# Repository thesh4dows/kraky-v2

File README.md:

# kraky-v2
Kraky2 is the second version of the DIY and open-hardware poject inspired by the Flipper Zero.
It uses the esp32-S3 microntroller to manage all the different modules like the NFC,RFID, and some.

The module is divided in 2 layers, the front one houses the esp32, Wifi and Sub-GHz antennas, buttons, IR and a part of the
power delivery system; the back one houses the NFC and RFID modules on top of the rest of the power delivery system.

Using the four buttons you can take advantage of all the modules that composes the kraky2, you can also use it connected to 
a battery or via the usb-c port that is integrated in the circuit.

I would suggest putting first the esp32 as is the most difficult part to put, then the others chip, all the capacitors, resistors, inductors and so on and for last all the
tht components because they are the ones that pass through the board so they are more simple to put.

I started this journey because i want to create a better version of my project kraky, and i'm doing it by first using smd components instead of the 
tht modules so i can do some expirience soldering very small parts and stopping using pre made modules but recreating them myself.
420.65
---

# Main Components
| Function | Component |
|--------|----------|
| Logic board | **ESP32-S3 N16R8** |
| wifi | **nrf24l01** |
| Sub-GHz | **CC1101** |
| RFID | **MFRC522** |
| NFC | **PN532** |
| Battery charger | **CN3163** |
| Battery | Li-ion |
| IR Receiver | **TSOP38238** |
| IR Transmitter | IR LED |
| microSD Slot | **MSD4A** |
| Buttons | 4 tactile buttons |
| Display | TFT Display |

---

# WIRING DIAGRAM

# ESP32

 # POWER DELIVERY SYSTEM

# IR

# WIFI

# SUB-GHZ

# MICROSD SLOT

# NFC

# RFID

# BUTTONS

# DISPLAY

---

# PCB

---

# 3D RENDER

---
# Responsible Use
Kraky2 is built to make it easier for anyone to explore and understand how multifunction electronic devices work in everyday life. It’s not intended for bypassing security systems or breaking any laws.

All features are implemented with an educational and experimental focus.

---

# Zine page

---

# Tools Used

- KiCad 10
- Fusion360
- PlatformIO
---
## Contributing

Kraky is an **open and educational project**.  
Feedback, suggestions, and improvements are always welcome.

---

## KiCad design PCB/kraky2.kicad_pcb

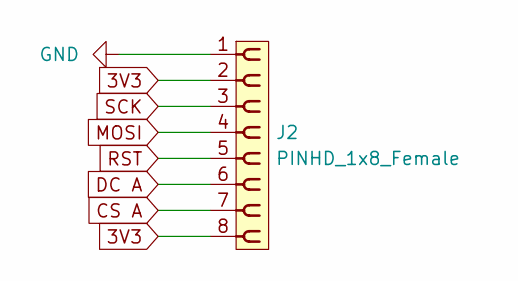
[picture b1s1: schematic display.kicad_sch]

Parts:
J2: PINHD_1x8_Female; PinSocket_1x08_P2.54mm_Vertical

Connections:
3V3: J2.2, J2.8; also elsewhere on the board
CS A: J2.7; also elsewhere on the board
DC A: J2.6; also elsewhere on the board
GND: J2.1; also elsewhere on the board
MOSI: J2.4; also elsewhere on the board
RST A: J2.5; also elsewhere on the board
SCK: J2.3; also elsewhere on the board

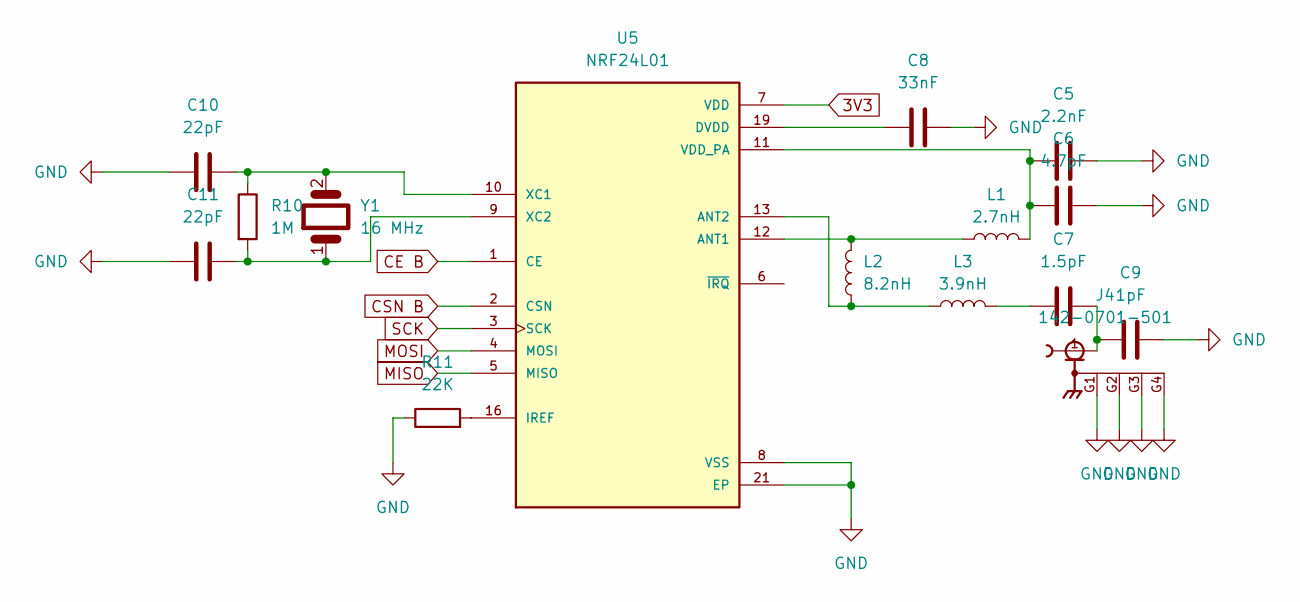
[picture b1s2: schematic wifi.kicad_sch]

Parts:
C5: 2.2nF; C_0805_2012Metric
C6: 4.7pF; C_0805_2012Metric
C7: 1.5pF; C_0805_2012Metric
C8: 33nF; C_0805_2012Metric
C9: 1pF; C_0805_2012Metric
C10, C11: 22pF; C_0805_2012Metric
J4: 142-0701-501; SMA_Molex_73251-1153_EdgeMount_Horizontal; PARTREV 7c
L1: 2.7nH; L_0805_2012Metric
L2: 8.2nH; L_0805_2012Metric
L3: 3.9nH; L_0805_2012Metric
R10: 1M; R_0805_2012Metric
R11: 22K; R_0805_2012Metric
U5: NRF24L01; QFN50P400X400X95-21N; PARTREV 2.0
Y1: 16 MHz; Crystal_SMD_5032-2Pin_5.0x3.2mm_HandSoldering

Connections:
3V3: U5.7 (VDD), U5.15 (VDD), U5.18 (VDD); also elsewhere on the board
CE B: U5.1 (CE); also elsewhere on the board
CSN B: U5.2 (CSN); also elsewhere on the board
GND: C5.2, C6.2, C8.2, C9.2, C10.1, C11.1, J4.G1, J4.G2, J4.G3, J4.G4, R11.1, U5.8 (VSS), U5.14 (VSS), U5.17 (VSS), U5.20 (VSS), U5.21 (EP); also elsewhere on the board
MISO: U5.5 (MISO); also elsewhere on the board
MOSI: U5.4 (MOSI); also elsewhere on the board
unnamed: C7.1, L3.2
unnamed: C7.2, C9.1, J4.1
unnamed: L1.1, L2.2, U5.12 (ANT1)
unnamed: L2.1, L3.1, U5.13 (ANT2)
unnamed: C8.1, U5.19 (DVDD)
unnamed: R11.2, U5.16 (IREF)
unnamed: C5.1, C6.1, L1.2, U5.11 (VDD_PA)
unnamed: C10.2, R10.1, U5.10 (XC1), Y1.2
unnamed: C11.2, R10.2, U5.9 (XC2), Y1.1
SCK: U5.3 (SCK); also elsewhere on the board

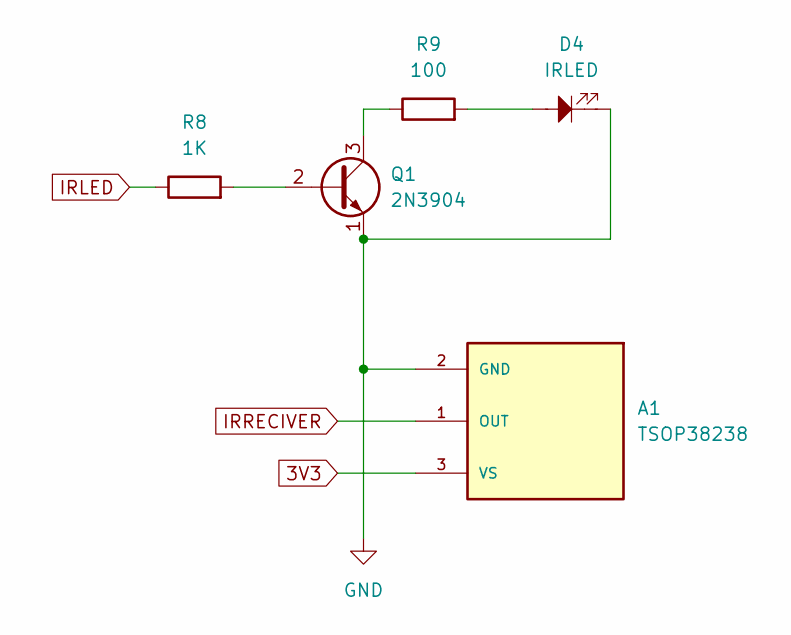
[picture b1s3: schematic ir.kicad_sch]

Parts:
A1: TSOP38238; XDCR_TSOP38238; PARTREV 1.7
D4: IRLED; WL-SISW_1002_15410294AA570
Q1: 2N3904; SOT-23_Handsoldering
R8: 1K; R_0805_2012Metric
R9: 100; R_0805_2012Metric

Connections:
3V3: A1.3 (VS); also elsewhere on the board
GND: A1.2 (GND), D4.1, Q1.1 (E); also elsewhere on the board
IRLED: R8.1; also elsewhere on the board
IRRECIVER: A1.1 (OUT); also elsewhere on the board
unnamed: D4.2, R9.2
unnamed: Q1.2 (B), R8.2
unnamed: Q1.3 (C), R9.1

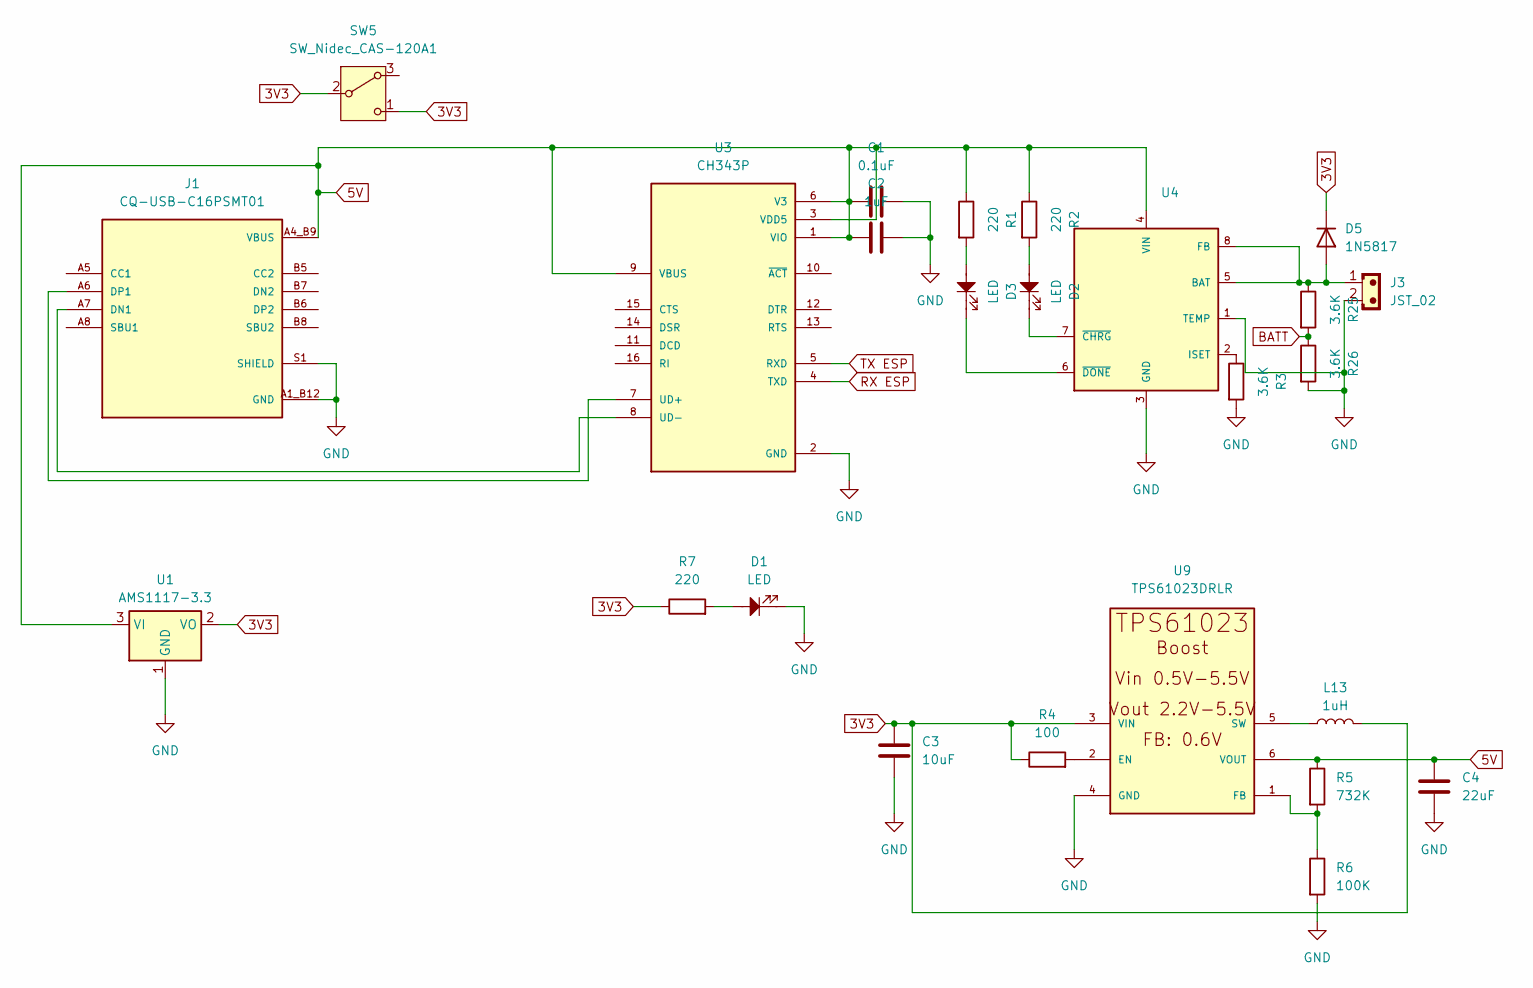
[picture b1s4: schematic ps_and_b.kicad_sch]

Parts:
C1: 0.1uF; C_0805_2012Metric
C2: 1uF; C_0805_2012Metric
C3: 10uF; C_0805_2012Metric
C4: 22uF; C_0805_2012Metric
D1, D2, D3: LED; LED_1206_3216Metric
D5: 1N5817; D_SMA_Handsoldering
J1: CQ-USB-C16PSMT01; SHENZHEN-CHUANGQIN-TECHNOLOGY_CQ-USB-C16PSMT01; PARTREV A
J3: JST_02; JST_EH_B2B-EH-A_1x02_P2.50mm_Vertical
L13: 1uH; L_0805_2012Metric
R1, R2, R7: 220; R_0805_2012Metric
R3, R25, R26: 3.6K; R_0805_2012Metric
R4: 100; R_0805_2012Metric
R5: 732K; R_0805_2012Metric
R6: 100K; R_0805_2012Metric
SW5: SW_Nidec_CAS-120A1; SW_Slide_SPDT_Angled_CK_OS102011MA1Q
U1: AMS1117-3.3; SOT-223-3_TabPin2
U3: CH343P; QFN50P300X300X80-17N; PARTREV 1E
U4: CN3063-SOIC8; SOIC8-1.27-5X4MM; MPN CN3063
U9: TPS61023DRLR; SOT563-ORI

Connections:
3V3: C3.1, D5.1 (K), L13.2, R4.1, R7.1, SW5.1 (C), SW5.2 (B), U1.2 (VO), U9.3 (VIN); also elsewhere on the board
5V: C1.1, C2.1, C4.1, J1.A4_B9 (VBUS), J1.B4_A9 (VBUS), R1.1, R2.1, R5.1, U1.3 (VI), U3.1 (VIO), U3.3 (VDD5), U3.6 (V3), U3.9 (VBUS), U4.4 (VIN), U9.6 (VOUT); also elsewhere on the board
BATT: R25.2, R26.1; also elsewhere on the board
GND: C1.2, C2.2, C3.2, C4.2, D1.1, J1.A1_B12 (GND), J1.B1_A12 (GND), J1.S1 (SHIELD), J1.S2 (SHIELD), J1.S3 (SHIELD), J1.S4 (SHIELD), J3.2, R3.2, R6.2, R26.2, U1.1 (GND), U3.2 (GND), U3.17 (GND), U4.1 (TEMP), U4.3 (GND), U9.4 (GND); also elsewhere on the board
unnamed: D1.2, R7.2
unnamed: D2.2, R2.2
unnamed: D3.2, R1.2
unnamed: D5.2 (A), J3.1, R25.1, U4.5 (BAT), U4.8 (FB)
unnamed: J1.A7 (DN1), U3.8 (UD-)
unnamed: J1.A6 (DP1), U3.7 (UD+)
unnamed: R3.1, U4.2 (ISET)
unnamed: D2.1, U4.7 (~CHRG)
unnamed: D3.1, U4.6 (~DONE)
unnamed: R4.2, U9.2 (EN)
unnamed: R5.2, R6.1, U9.1 (FB)
unnamed: L13.1, U9.5 (SW)
RX ESP: U3.4 (TXD); also elsewhere on the board
TX ESP: U3.5 (RXD); also elsewhere on the board

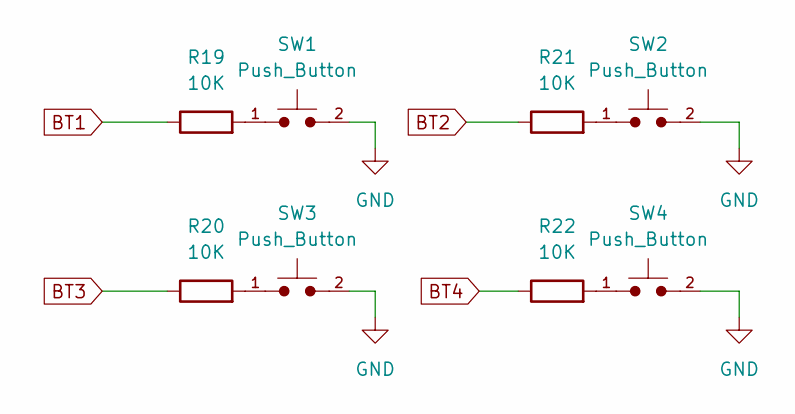
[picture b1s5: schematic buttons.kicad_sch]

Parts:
R19, R20, R21, R22: 10K; R_0805_2012Metric
SW1, SW2, SW3, SW4: Push_Button; SW_SPST_PTS645Sx43SMTR92

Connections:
BT1: R19.1; also elsewhere on the board
BT2: R21.1; also elsewhere on the board
BT3: R20.1; also elsewhere on the board
BT4: R22.1; also elsewhere on the board
GND: SW1.2, SW2.2, SW3.2, SW4.2; also elsewhere on the board
unnamed: R19.2, SW1.1
unnamed: R20.2, SW3.1
unnamed: R21.2, SW2.1
unnamed: R22.2, SW4.1

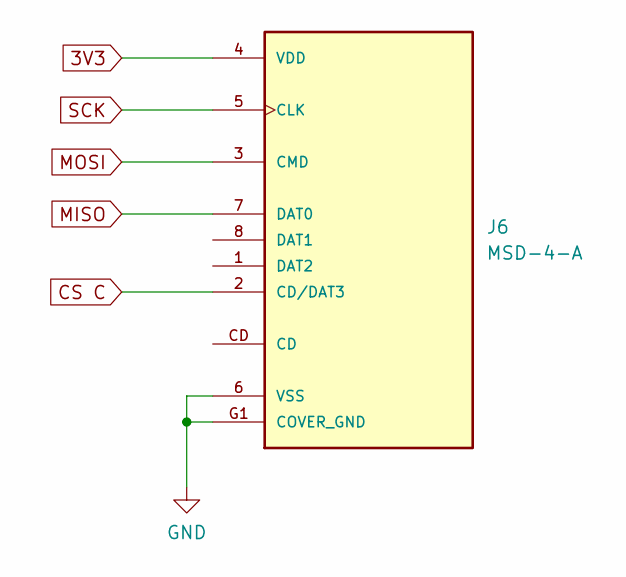
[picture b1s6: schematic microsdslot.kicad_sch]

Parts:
J6: MSD-4-A; CUI_MSD-4-A; PARTREV 1.0

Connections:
3V3: J6.4 (VDD); also elsewhere on the board
CS C: J6.2 (CD/DAT3); also elsewhere on the board
GND: J6.6 (VSS), J6.G1 (COVER_GND), J6.G2 (COVER_GND), J6.G3 (COVER_GND), J6.G4 (COVER_GND); also elsewhere on the board
MISO: J6.7 (DAT0); also elsewhere on the board
MOSI: J6.3 (CMD); also elsewhere on the board
SCK: J6.5 (CLK); also elsewhere on the board

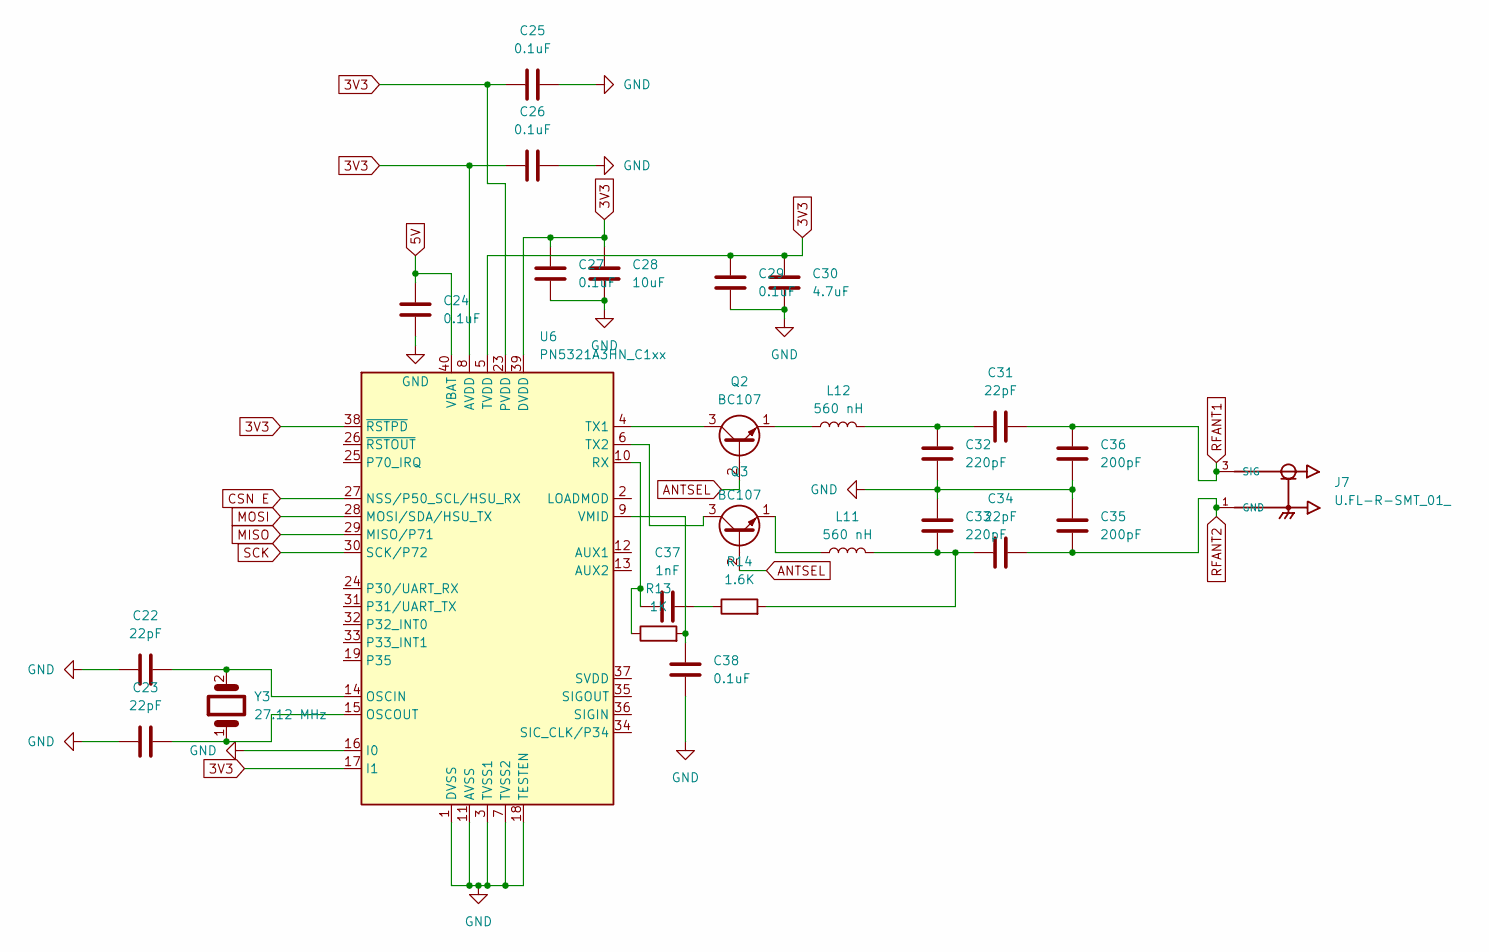
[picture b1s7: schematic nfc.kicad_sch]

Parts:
C22, C23, C31, C34: 22pF; C_0805_2012Metric
C24, C25, C26, C27, C29, C38: 0.1uF; C_0805_2012Metric
C28: 10uF; C_0805_2012Metric
C30: 4.7uF; C_0805_2012Metric
C32, C33: 220pF; C_0805_2012Metric
C35, C36: 200pF; C_0805_2012Metric
C37: 1nF; C_0805_2012Metric
J7: U.FL-R-SMT_01_; HRS_U.FL-R-SMT_01_
L11, L12: 560 nH; L_0805_2012Metric
Q2, Q3: BC107; SOT-23_Handsoldering
R13: 1K; R_0805_2012Metric
R14: 1.6K; R_0805_2012Metric
U6: PN5321A3HN_C1xx; HVQFN-40-1EP_6x6mm_P0.5mm_EP4.1x4.1mm_ThermalVias
Y3: 27.12 MHz; Crystal_SMD_5032-2Pin_5.0x3.2mm_HandSoldering

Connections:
3V3: C25.1, C26.1, C27.1, C28.1, C29.1, C30.1, U6.5 (TVDD), U6.8 (AVDD), U6.17 (I1), U6.23 (PVDD), U6.38 (~RSTPD), U6.39 (DVDD); also elsewhere on the board
5V: C24.1, U6.40 (VBAT); also elsewhere on the board
ANTSEL: Q2.2 (B), Q3.2 (B); also elsewhere on the board
CSN E: U6.27 (NSS/P50_SCL/HSU_RX); also elsewhere on the board
GND: C22.1, C23.1, C24.2, C25.2, C26.2, C27.2, C28.2, C29.2, C30.2, C32.1, C33.2, C35.1, C36.2, C38.2, U6.1 (DVSS), U6.3 (TVSS1), U6.7 (TVSS2), U6.11 (AVSS), U6.16 (I0), U6.18 (TESTEN), U6.41 (AVSS); also elsewhere on the board
MISO: U6.29 (MISO/P71); also elsewhere on the board
MOSI: U6.28 (MOSI/SDA/HSU_TX); also elsewhere on the board
unnamed: C31.1, C32.2, L12.2
unnamed: C33.1, C34.1, L11.2, R14.2
unnamed: C37.2, R14.1
unnamed: Q2.3 (C), U6.4 (TX1)
unnamed: L12.1, Q2.1 (E)
unnamed: Q3.3 (C), U6.6 (TX2)
unnamed: L11.1, Q3.1 (E)
unnamed: C22.2, U6.14 (OSCIN), Y3.2
unnamed: C23.2, U6.15 (OSCOUT), Y3.1
unnamed: C37.1, R13.1, U6.10 (RX)
unnamed: C38.1, R13.2, U6.9 (VMID)
RFANT1: C31.2, C36.1, J7.3 (SIG); also elsewhere on the board
RFANT2: C34.2, C35.2, J7.1 (GND), J7.2 (GND); also elsewhere on the board
SCK: U6.30 (SCK/P72); also elsewhere on the board

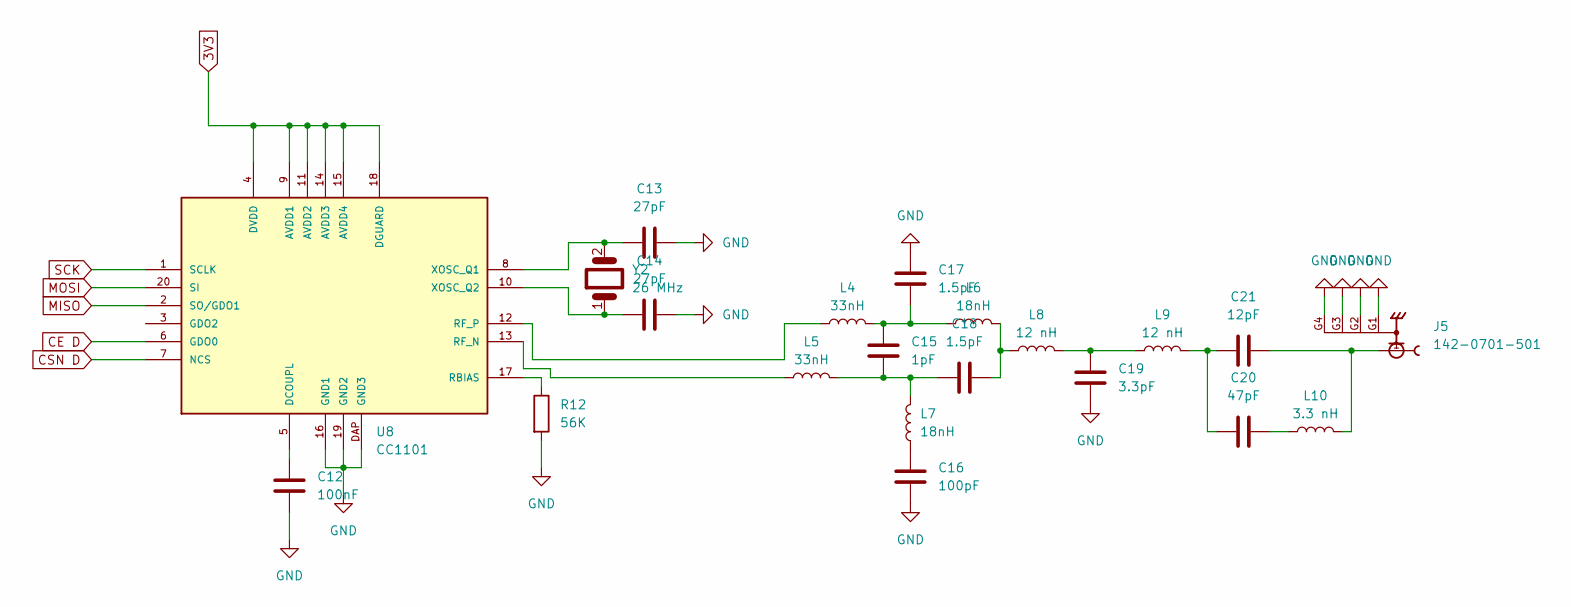
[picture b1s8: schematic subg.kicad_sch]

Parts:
C12: 100nF; C_0805_2012Metric
C13, C14: 27pF; C_0805_2012Metric
C15: 1pF; C_0805_2012Metric
C16: 100pF; C_0805_2012Metric
C17, C18: 1.5pF; C_0805_2012Metric
C19: 3.3pF; C_0805_2012Metric
C20: 47pF; C_0805_2012Metric
C21: 12pF; C_0805_2012Metric
J5: 142-0701-501; SMA_Molex_73251-1153_EdgeMount_Horizontal; PARTREV 7c
L4, L5: 33nH; L_0805_2012Metric
L6, L7: 18nH; L_0805_2012Metric
L8, L9: 12 nH; L_0805_2012Metric
L10: 3.3 nH; L_0805_2012Metric
R12: 56K; R_0805_2012Metric
U8: CC1101; QLP20
Y2: 26 MHz; Crystal_SMD_5032-2Pin_5.0x3.2mm_HandSoldering

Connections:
3V3: U8.4 (DVDD), U8.9 (AVDD1), U8.11 (AVDD2), U8.14 (AVDD3), U8.15 (AVDD4), U8.18 (DGUARD); also elsewhere on the board
CE D: U8.6 (GDO0); also elsewhere on the board
CSN D: U8.7 (NCS); also elsewhere on the board
GND: C12.1, C13.2, C14.2, C16.1, C17.2, C19.1, J5.G1, J5.G2, J5.G3, J5.G4, R12.2, U8.16 (GND1), U8.19 (GND2), U8.DAP (GND3); also elsewhere on the board
MISO: U8.2 (SO/GDO1); also elsewhere on the board
MOSI: U8.20 (SI); also elsewhere on the board
unnamed: C15.1, C18.2, L5.2, L7.2
unnamed: C15.2, C17.1, L4.2, L6.1
unnamed: C16.2, L7.1
unnamed: C18.1, L6.2, L8.1
unnamed: C19.2, L8.2, L9.1
unnamed: C20.1, C21.1, L9.2
unnamed: C20.2, L10.1
unnamed: C21.2, J5.1, L10.2
unnamed: C12.2, U8.5 (DCOUPL)
unnamed: R12.1, U8.17 (RBIAS)
unnamed: L5.1, U8.13 (RF_N)
unnamed: L4.1, U8.12 (RF_P)
unnamed: C13.1, U8.8 (XOSC_Q1), Y2.2
unnamed: C14.1, U8.10 (XOSC_Q2), Y2.1
SCK: U8.1 (SCLK); also elsewhere on the board

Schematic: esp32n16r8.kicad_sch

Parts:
R23, R24: 10K; R_0805_2012Metric
SW6: RESET; SW_SPST_EVQPE1
SW7: BOOT; SW_SPST_EVQPE1
U11: ESP32-S3-WROOM-1

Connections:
3V3: U11.2 (3V3); also elsewhere on the board
ANTSEL: U11.5 (IO5); also elsewhere on the board
ANTSEL1: U11.7 (IO7); also elsewhere on the board
BATT: U11.17 (IO9); also elsewhere on the board
BT1: U11.31 (IO38); also elsewhere on the board
BT2: U11.32 (IO39); also elsewhere on the board
BT3: U11.33 (IO40); also elsewhere on the board
BT4: U11.34 (IO41); also elsewhere on the board
CE B: U11.4 (IO4); also elsewhere on the board
CE D: U11.38 (IO2); also elsewhere on the board
CS A: U11.16 (IO46); also elsewhere on the board
CS C: U11.12 (IO8); also elsewhere on the board
CSN B: U11.25 (IO48); also elsewhere on the board
CSN D: U11.15 (IO3); also elsewhere on the board
CSN E: U11.39 (IO1); also elsewhere on the board
CSN F: U11.6 (IO6); also elsewhere on the board
DC A: U11.24 (IO47); also elsewhere on the board
GND: SW6.1, SW7.1, U11.1 (GND), U11.40 (GND), U11.41 (GND); also elsewhere on the board
IRLED: U11.35 (IO42); also elsewhere on the board
IRRECIVER: U11.26 (IO45); also elsewhere on the board
MISO: U11.10 (IO17); also elsewhere on the board
MOSI: U11.11 (IO18); also elsewhere on the board
unnamed: R23.1, SW7.2
unnamed: R24.1, SW6.2
unnamed: R23.2, U11.27 (IO0)
RST: R24.2, U11.3 (EN)
RST A: U11.18 (IO10); also elsewhere on the board
RX ESP: U11.36 (RXD0); also elsewhere on the board
SCK: U11.23 (IO21); also elsewhere on the board
TX ESP: U11.37 (TXD0); also elsewhere on the board

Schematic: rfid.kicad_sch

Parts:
C39, C40, C41, C42, C43, C44, C45, C46, C47, C48: 1uF; C_0805_2012Metric
L14, L15: 1 mH; L_0805_2012Metric
Q4, Q5: BC107; SOT-23_Handsoldering
R15, R16, R17, R18: 1K; R_0805_2012Metric
U10: MFRC522; QFN50P500X500X100-33N; PARTREV 3.9
Y4: 27.12 MHz; Crystal_SMD_5032-2Pin_5.0x3.2mm_HandSoldering

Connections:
3V3: U10.2 (PVDD), U10.3 (DVDD), U10.6 (~NRSTPD), U10.9 (SVDD), U10.12 (TVDD), U10.15 (AVDD); also elsewhere on the board
ANTSEL1: Q4.2 (B), Q5.2 (B); also elsewhere on the board
CSN F: U10.24 (SDA/NSS/RX); also elsewhere on the board
GND: C40.2, C41.2, C48.2, U10.4 (DVSS), U10.5 (PVSS), U10.10 (TVSS), U10.14 (TVSS), U10.18 (AVSS); also elsewhere on the board
MISO: U10.31 (D7/SCL/MISO/TX); also elsewhere on the board
MOSI: U10.30 (D6/ADR_0/MOSI/MX); also elsewhere on the board
unnamed: C39.2, R17.1
unnamed: C42.1, C45.1, L15.2
unnamed: C42.2, C47.1, R15.1
unnamed: C43.1, C44.2, L14.2
unnamed: C43.2, C46.2, R18.1
unnamed: C44.1, C45.2
unnamed: C46.1, C47.2
unnamed: Q4.3 (C), R17.2, U10.11 (TX1)
unnamed: L14.1, Q4.1 (E)
unnamed: Q5.3 (C), U10.13 (TX2)
unnamed: L15.1, Q5.1 (E)
unnamed: C41.1, U10.21 (OSCIN), Y4.2
unnamed: C48.1, U10.22 (OSCOUT), Y4.1
unnamed: C39.1, R16.1, U10.17 (RX)
unnamed: C40.1, R16.2, U10.16 (VMID)
RFANT1: R15.2; also elsewhere on the board
RFANT2: R18.2; also elsewhere on the board
SCK: U10.29 (D5/ADR_1/SCK/DTRQ); also elsewhere on the board

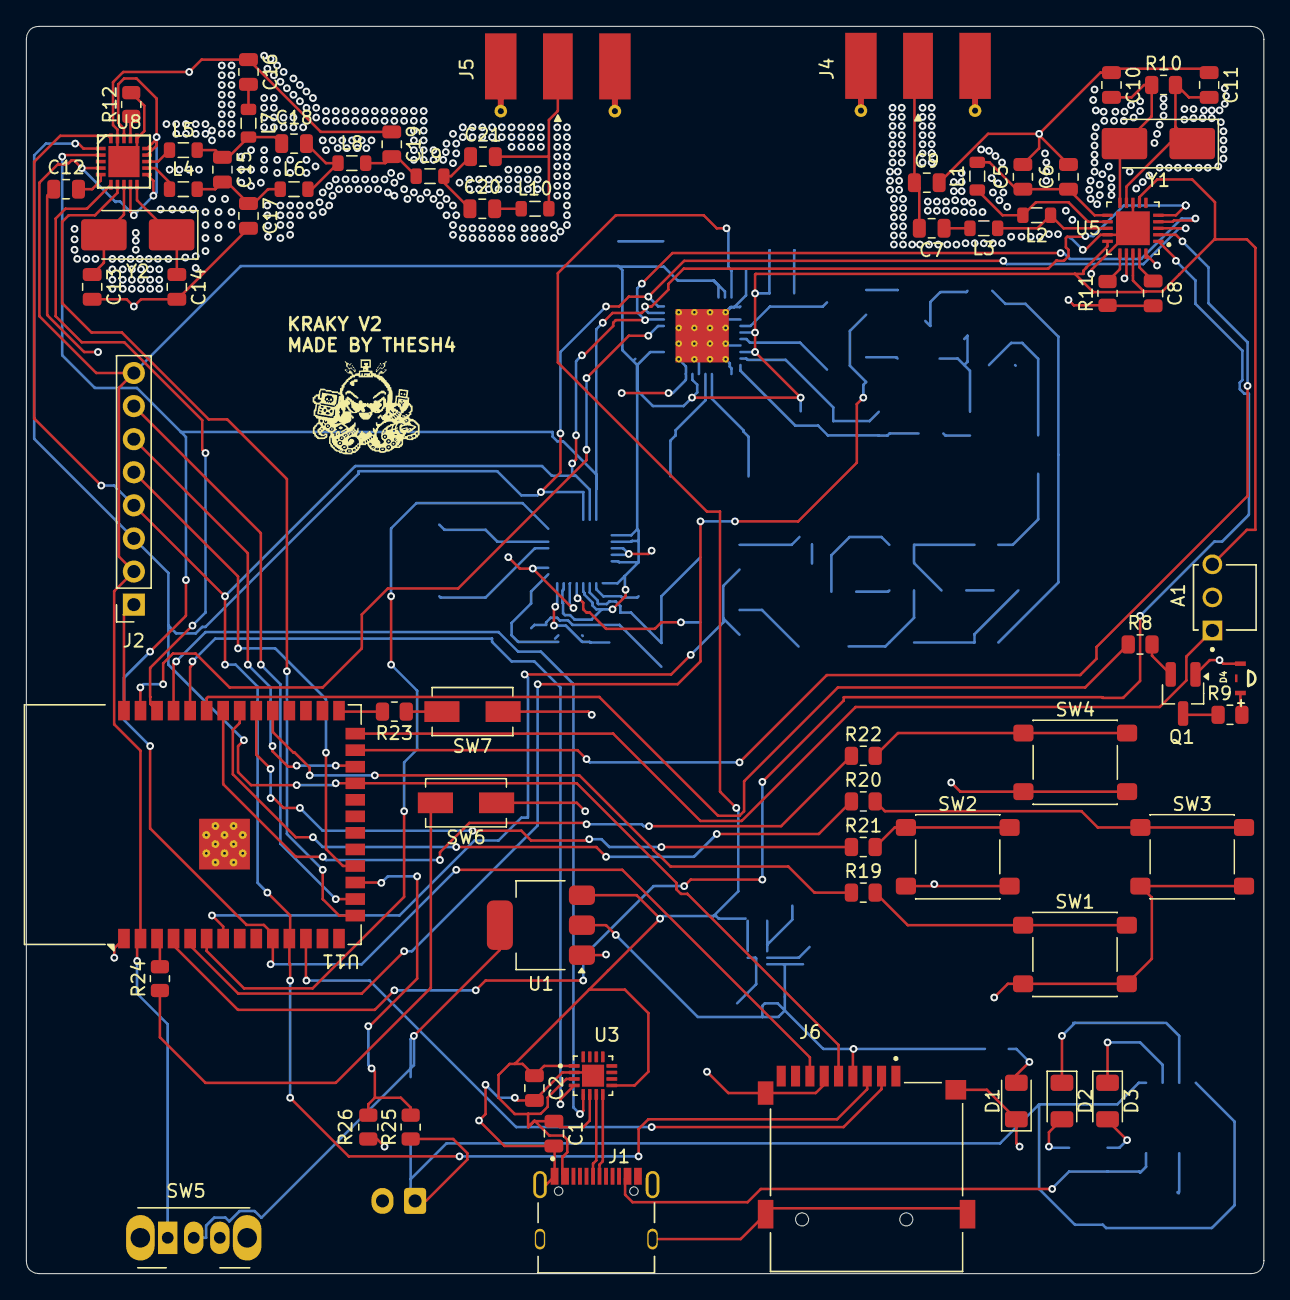
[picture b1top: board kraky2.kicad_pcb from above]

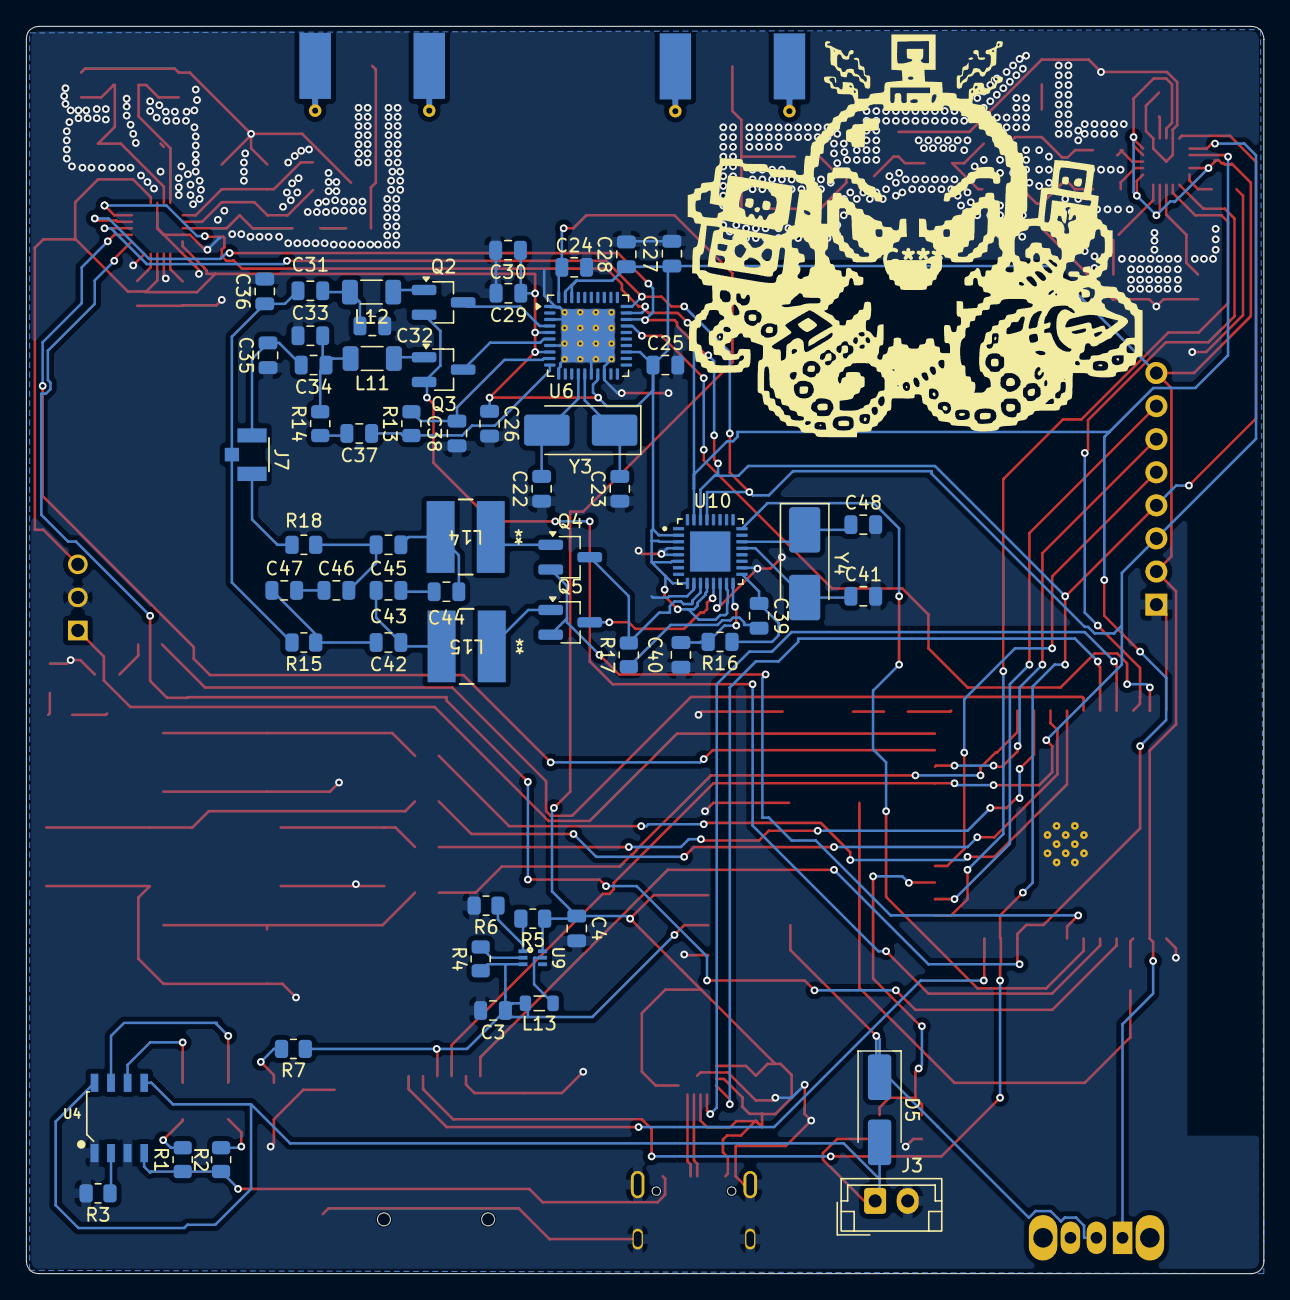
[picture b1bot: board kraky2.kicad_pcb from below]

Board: 2 copper layers, 95.0 x 95.8 mm, 127 parts (60 on the bottom side), 101 nets.

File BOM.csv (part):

name,value ,link,description,cost,quantity,added
resistor,,,,,,
R1,220,https://it.aliexpress.com/item/1005010070793079.html?spm=a2g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,805,1.45,3,
R2,220,R1,805,R1,R1,
R3,3.6K,https://it.aliexpress.com/item/1005010070793079.html?spm=a2g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,805,1.45,1,
R4,100,https://it.aliexpress.com/item/1005010070793079.html?spm=a2g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,805,1.45,2,
R5,732K,https://it.aliexpress.com/item/1005005184230104.html?spm=a2g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,805,2.07,1,
R6,100K,https://it.aliexpress.com/item/1005010070793079.html?spm=a2g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,805,1.45,3,
R7,220,R1,805,R1,R1,
R8,1K,https://it.aliexpress.com/item/1005010070793079.html?spm=a2g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,805,1.45,6,
R9,100,R4,805,R4,R4,
R10,1M,https://it.aliexpress.com/item/1005010070793079.html?spm=a2g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,805,1.46,1,
R11,22K,https://it.aliexpress.com/item/1005010070793079.html?spm=a2g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,805,1.45,1,
R12,56K,https://it.aliexpress.com/item/1005010070793079.html?spm=a2g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,805,1.45,1,
R13,1K,R8,805,R8,R8,
R14,1.6K,https://it.aliexpress.com/item/1005010070793079.html?spm=a2g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,805,1.45,1,
R15,1K,R8,805,R8,R8,
R16,1K,R8,805,R8,R8,
R17,1K,R8,805,R8,R8,
R18,1K,R8,805,R8,R8,
R19,10K,https://it.aliexpress.com/item/1005010070793079.html?spm=a2g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,805,1.45,6,
R20,10K,R19,805,R19,R19,
R21,10K,R19,805,R19,R19,
R22,10K,R19,805,R19,R19,
R23,10K,R19,805,R19,R19,
R24,10K,R19,805,R19,R19,
R25,100K,R6,805,R6,R6,
R26,100K,R6,805,R6,R6,
capacitor,,,,,,
C1,0.1 uF,https://it.aliexpress.com/item/1005005929029743.html?spm=a2g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,805,1.22,7,
C2,1 uF,https://it.aliexpress.com/item/1005005929029743.html?spm=a2g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,805,1.6,11,
C3,10 uF,https://it.aliexpress.com/item/1005005929029743.html?spm=a2g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,805,1.46,2,
C4,22 uF,https://it.aliexpress.com/item/1005005929029743.html?spm=a2g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,805,1.6,1,
C5,2.2 nF,https://it.aliexpress.com/item/1005005929029743.html?spm=a2g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,805,1.36,1,
C6,4.7 pF,https://it.aliexpress.com/item/1005005929029743.html?spm=a2g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,805,1.36,1,
C7,1.5 pF,https://it.aliexpress.com/item/1005005929029743.html?spm=a2g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,805,1.36,3,
C8,33 nF,https://it.aliexpress.com/item/1005005929029743.html?spm=a2g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,805,1.37,1,
C9,1 pF,https://it.aliexpress.com/item/1005005929029743.html?spm=a2g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,805,1.36,2,
C10,22 pF,https://it.aliexpress.com/item/1005005929029743.html?spm=a2g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,805,1.38,6,
C11,22 pF,C10,805,C10,C10,
C12,100 nF,https://it.aliexpress.com/item/1005005929029743.html?spm=a2g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,805,1.21,1,
C13,27 pF,https://it.aliexpress.com/item/1005005929029743.html?spm=a2g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,805,1.38,2,
C14,27 pF,C13,805,C13,C13,
C15,1 pF,C9,805,C9,C9,
C16,100 pF,https://it.aliexpress.com/item/1005005929029743.html?spm=a2g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,805,1.36,1,
C17,1.5 pF,C7,805,C7,C7,
C18,1.5pF,C7,805,C7,C7,
C19,3.3 pF,https://it.aliexpress.com/item/1005005929029743.html?spm=a2g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,805,1.38,1,
C20,47 pF,https://it.aliexpress.com/item/1005005929029743.html?spm=a2g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,805,1.38,1,
C21,12 pF,https://it.aliexpress.com/item/1005005929029743.html?spm=a2g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,805,1.38,1,
C22,22 pF,C10,805,C10,C10,
C23,22 pF,C10,805,C10,C10,
C24,0.1 uF,C1,805,C1,C1,
C25,0.1 uF,C1,805,C1,C1,
C26,0.1 uF,C1,805,C1,C1,
C27,0.1 uF,C1,805,C1,C1,
C28,10 uF,C3,805,C3,C3,
C29,0.1 uF,C1,805,C1,C1,
C30,4.7 uF,https://it.aliexpress.com/item/1005005929029743.html?spm=a2g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,805,1.6,1,
C31,22 pF,C10,805,C10,C10,
C32,220 pF,https://it.aliexpress.com/item/1005005929029743.html?spm=a2g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,805,1.38,2,
C33,220 pF,C32,805,C32,C32,
C34,22 pF,C10,805,C10,C10,
C35,200 pF,https://it.aliexpress.com/item/1005005929029743.html?spm=a2g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,805,1.38,2,
C36,200 pF,C35,805,C35,C35,
C37,1 nF,https://it.aliexpress.com/item/1005005929029743.html?spm=a2g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,805,1.37,1,
C38,0.1 uF,C1,805,C1,C1,
C39,1 uF,C2,805,C2,C2,
C40,1 uF,C2,805,C2,C2,
C41,1 uF,C2,805,C2,C2,
C42,1 uF,C2,805,C2,C2,
C43,1 uF,C2,805,C2,C2,
C44,1 uF,C2,805,C2,C2,
C45,1 uF,C2,805,C2,C2,
C46,1 uF,C2,805,C2,C2,
C47,1 uF,C2,805,C2,C2,
C48,1 uF,C2,805,C2,C2,
inductor,,,,,,
L1,2.7 nH,https://it.aliexpress.com/item/1005003062755166.html?spm=a2g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,805,1.65,1,
L2,8.2 nH,https://it.aliexpress.com/item/1005003062755166.html?spm=a2g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,805,1.62,1,
L3,3.9 nH,https://it.aliexpress.com/item/1005003062755166.html?spm=a2g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,805,1.62,1,
L4,33 nH,https://it.aliexpress.com/item/1005006165931240.html?spm=a2g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,805,5.47,2,
L5,33 nH,L4,805,L4,L4,
L6,18 nH,https://it.aliexpress.com/item/1005003062755166.html?spm=a2g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,805,1.62,2,
L7,18 nH,L6,805,L6,L6,
L8,12 nH,https://it.aliexpress.com/item/1005003062755166.html?spm=a2g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,805,1.65,2,
L9,12 nH,L8,805,L8,L8,
L10,3.3 nH,https://it.aliexpress.com/item/1005003062755166.html?spm=a2g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,805,1.62,1,
L11,560 nH,https://it.aliexpress.com/item/1005003091167117.html?spm=a2g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,1210,1.99,2,
L12,560 nH,L11,1210,L11,L11,
L13,1 uH,https://it.aliexpress.com/item/1005003827404196.html?spm=a2g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,805,3.89,1,
L14,1 mH,https://it.aliexpress.com/item/4001191068539.html?spm=a2g0o.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,805,1.6,2,
L15,1 mH,L14,805,L14,L14,
crystal,,,,,,
Y1,16 MHz,https://it.aliexpress.com/item/1005007210644647.html?spm=a2g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,5032,3.16,1,
Y2,26 MHz,https://it.aliexpress.com/item/1005004711354176.html?spm=a2g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,5032,2.79,1,
Y3,27.12 MHz,https://it.aliexpress.com/item/1005004711354176.html?spm=a2g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,5032,2.75,2,
Y4,27.12MHz,Y3,5032,Y3,Y3,
buttons,,,,,,
SW1,navigation,https://it.aliexpress.com/item/1005006870284823.html?spm=a2g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,smd  6x6 mm,1.69,4,
SW2,navigation,SW1,smd  6x6 mm,SW1,SW1,
SW3,navigation,SW1,smd  6x6 mm,SW1,SW1,
SW4,navigation,SW1,smd  6x6 mm,SW1,SW1,
SW5,on/off,https://it.aliexpress.com/item/1005004328667818.html?spm=a2g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,tht 3 way switch,2.72,1,
SW6,RESET,https://it.aliexpress.com/item/1005008404608815.html?spm=a2g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,smd  6x3 mm,2.35,2,
SW7,BOOT,SW6,smd  6x3 mm,,SW6,
modules,,,,,,
U1,AMS1117-3.3,https://it.aliexpress.com/item/1005007027620474.html?spm=a2g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,voltage regulator,1.25,1,
U2,ESP32-S3-WROOM-1-N4R2,https://it.aliexpress.com/item/1005006214506085.html?spm=a2g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,ESP32 S3 N16R8,4.99,1,
U3,CH343P,https://it.aliexpress.com/item/1005009691777003.html?spm=a2g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,com converter,4.54,1,
U4,CN3063-SOIC8,https://it.aliexpress.com/item/1005006908180461.html?spm=a2g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,battery protection,2.43,1,
U5,NRF24L01,https://it.aliexpress.com/item/1005008669394507.html?spm=a2g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,wifi module,6.02,1,
U6,PN5321A3HN_C1xx,https://it.aliexpress.com/item/1005012051748463.html?spm=a2g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,nfc module,6.6,1,
ext,NFC_ANTENNA,https://it.aliexpress.com/item/1005007698497375.html?spm=a2g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,nfc antenna,8.53,1,
U8,CC1101,https://it.aliexpress.com/item/1005007128993296.html?spm=a2g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,subG module,1.89,1,
U9,TPS61023DRLR,https://it.aliexpress.com/item/1005009341066247.html?spm=a2g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,voltage booster,2.73,1,
U10,MFRC522,https://it.aliexpress.com/item/1005006882991356.html?spm=a2g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,rfid chip,5.62,1,
leds,,,,,,
D1,LED,https://it.aliexpress.com/item/32868897187.html?spm=a2g0o.pr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,1206,2.8,1,
D2,LED,https://it.aliexpress.com/item/1005007189026364.html?spm=a2g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,1206,1.55,1,
D3,LED,https://it.aliexpress.com/item/1005007189026364.html?spm=a2g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,1206,1.46,1,
D4,IRLED,https://it.aliexpress.com/item/1005010507118978.html?spm=a2g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,IR led,4.89,1,
transistors,,,,,,
Q1,2N3904,https://it.aliexpress.com/item/1005006501709413.html?spm=a2g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,IR transistor,1.17,1,
Q2,BC817,https://it.aliexpress.com/item/1005006943124825.html?spm=a2g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,Antenna transistor,1.17,4,
Q3,BC817,Q2,Antenna transistor,Q2,Q2,
Q4,BC817,Q2,Antenna transistor,Q2,Q2,
Q5,BC817,Q2,Antenna transistor,Q2,Q2,
diodes,,,,,,
D5,1N5817,https://it.aliexpress.com/item/1005006884142108.html?spm=a2g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,smd,1.69,1,
others,,,,,,
A1,TSOP38238,https://it.aliexpress.com/item/1005008745425158.html?spm=a2g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,IR reciver,2.8,1,
J1,CQ-USB-C16PSMT01,https://it.aliexpress.com/item/1005010643898257.html?spm=a2g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,USB-C port,2.27,1,
J2,PINHD_1x8_Female,https://it.aliexpress.com/item/1005009269759277.html?spm=a2g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,display,3.08,1,
J3,JST_02,https://it.aliexpress.com/item/1005009883885132.html?spm=a2g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,battery plug,2.22,1,
J4,142-0701-501,https://it.aliexpress.com/item/1005009514982478.html?spm=a2g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,antenna,4.79,2,
J5,142-0701-501,J4,antenna,J4,J4,
battery,li-on battery,https://it.aliexpress.com/item/1005009932615983.html?spm=a2g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,inr18650,4.91,1,
J6,MSD-4-A,https://it.aliexpress.com/item/1005006273533788.html?spm=a2g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,microsd port,2.24,1,
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
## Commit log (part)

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2026-04-29 Revise component details in README.md
    Updated component specifications for clarity and accuracy.
2026-05-04 Add USB-C pinout information to README
2026-05-04 Update FT232RQ chip reference in README
2026-05-21 Rename display.kicad_sch to PCB/display.kicad_sch
2026-05-21 Rename buttons.kicad_sch to PCB/buttons.kicad_sch
2026-05-21 Rename esp32n16r8.kicad_sch to PCB/esp32n16r8.kicad_sch
2026-05-21 Rename ir.kicad_sch to PCB/ir.kicad_sch
2026-05-21 Rename kraky2.kicad_pcb to PCB/kraky2.kicad_pcb
2026-05-21 Rename kraky2.kicad_prl to PCB/kraky2.kicad_prl
2026-05-21 Rename kraky2.kicad_pro to PCB/kraky2.kicad_pro
2026-05-21 Rename kraky2.kicad_sch to PCB/kraky2.kicad_sch
2026-05-21 Rename microsdslot.kicad_sch to PCB/microsdslot.kicad_sch
2026-05-21 Rename nfc.kicad_sch to PCB/nfc.kicad_sch
2026-05-21 Rename ps_and_b.kicad_sch to PCB/ps_and_b.kicad_sch
2026-05-21 Rename rfid.kicad_sch to PCB/rfid.kicad_sch
2026-05-21 Rename subg.kicad_sch to PCB/subg.kicad_sch
2026-05-21 Rename wifi.kicad_sch to PCB/wifi.kicad_sch
2026-05-21 Rename PCB/buttons.kicad_sch to PCB/Schematic/buttons.kicad_sch
2026-05-21 Rename PCB/display.kicad_sch to PCB/Schematic/display.kicad_sch
2026-05-21 Rename PCB/esp32n16r8.kicad_sch to PCB/Schematic/esp32n16r8.kicad_sch
2026-05-21 Rename PCB/ir.kicad_sch to PCB/Schematic/ir.kicad_sch
2026-05-21 Rename PCB/kraky2.kicad_sch to PCB/Schematic/kraky2.kicad_sch
2026-05-21 Rename PCB/microsdslot.kicad_sch to PCB/Schematic/microsdslot.kicad_sch
2026-05-21 Rename PCB/nfc.kicad_sch to PCB/Schematic/nfc.kicad_sch
2026-05-21 Rename PCB/ps_and_b.kicad_sch to PCB/Schematic/ps_and_b.kicad_sch
2026-05-21 Rename PCB/rfid.kicad_sch to PCB/Schematic/rfid.kicad_sch
2026-05-21 Rename PCB/subg.kicad_sch to PCB/Schematic/subg.kicad_sch
2026-05-21 Rename PCB/wifi.kicad_sch to PCB/Schematic/wifi.kicad_sch
2026-05-21 Rename kraky2.step to 3D RENDER/kraky2.step
2026-05-21 Update issue templates
2026-05-26 Rename main (1).cpp to firmware/main .cpp
2026-05-26 Rename kraky2.csv to BOM.csv
2026-05-26 Rename kraky2.f3d to kraky2.f3d
2026-05-26 Rename kraky2.step to kraky2.step
2026-05-26 Rename firmware/main .cpp to firmware/scr/main .cpp
2026-05-26 Rename main .cpp to main.cpp
2026-06-01 test menu
2026-06-01 Rename firmware/scr/menuv1.ino to firmware/scr/tests/menuv1.ino
2026-06-01 do not function
2026-06-04 Rename kraky2 poster (2).pdf to kraky2 poster.pdf
2026-06-04 Rename PCB/birNoktaSekizInchTFTEkran.stp to PCB/3D_renderes/birNoktaSekizInchTFTEkran.stp
2026-06-04 Rename kraky2 poster (1).pdf to kraky2 poster.pdf
2026-06-05 Create LICENSE
2026-06-15 Rename kraky2 poster (3).pdf to kraky2 poster.pdf
